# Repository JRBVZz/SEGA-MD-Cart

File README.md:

#### SEGA MD Cart - картридж для SEGA MegaDrive/Genesis

Простой картридж объемом до 4MB (32Mbit) без сохранений, который можно перезаписывать с помощью программатора [FlashKit MD](https://github.com/JRBVZz/Flashkit-MD).

10.02.2026. Добавил проект PCB с возможностью установки памяти MX29L3211 в корпусе SOP-44.

Для хранения данных используется flash память в корпусе TSOP-48 - S29GL032, MX29LV320, M29W320 и др. Для игр до 2MB можно использовать память меньшего объема.

**Параметры для изготовления PCB**  
* 2 слоя
* Толщина PCB: 1.6 мм
* Рекомендуется ENIG покрытие контактов краевого разъема

**Схемы**  
[Schematic PDF](SEGA-Cart-Info/SEGA-Cart-Schematic.pdf)  
[Schematic PDF SOP](SEGA-Cart-Info/SEGA-Cart-SOP-Schematic.pdf)

**Интерактивный BOM**  
[BoM](SEGA-Cart-Info/SEGA-Cart-iBOM.html) (для корректного просмотра нужно скачать raw файл)  
[BoM-SOP](SEGA-Cart-Info/SEGA-Cart-SOP-iBOM.html) (для корректного просмотра нужно скачать raw файл)

Проект создан в [**KiCad 9**](https://www.kicad.org/).

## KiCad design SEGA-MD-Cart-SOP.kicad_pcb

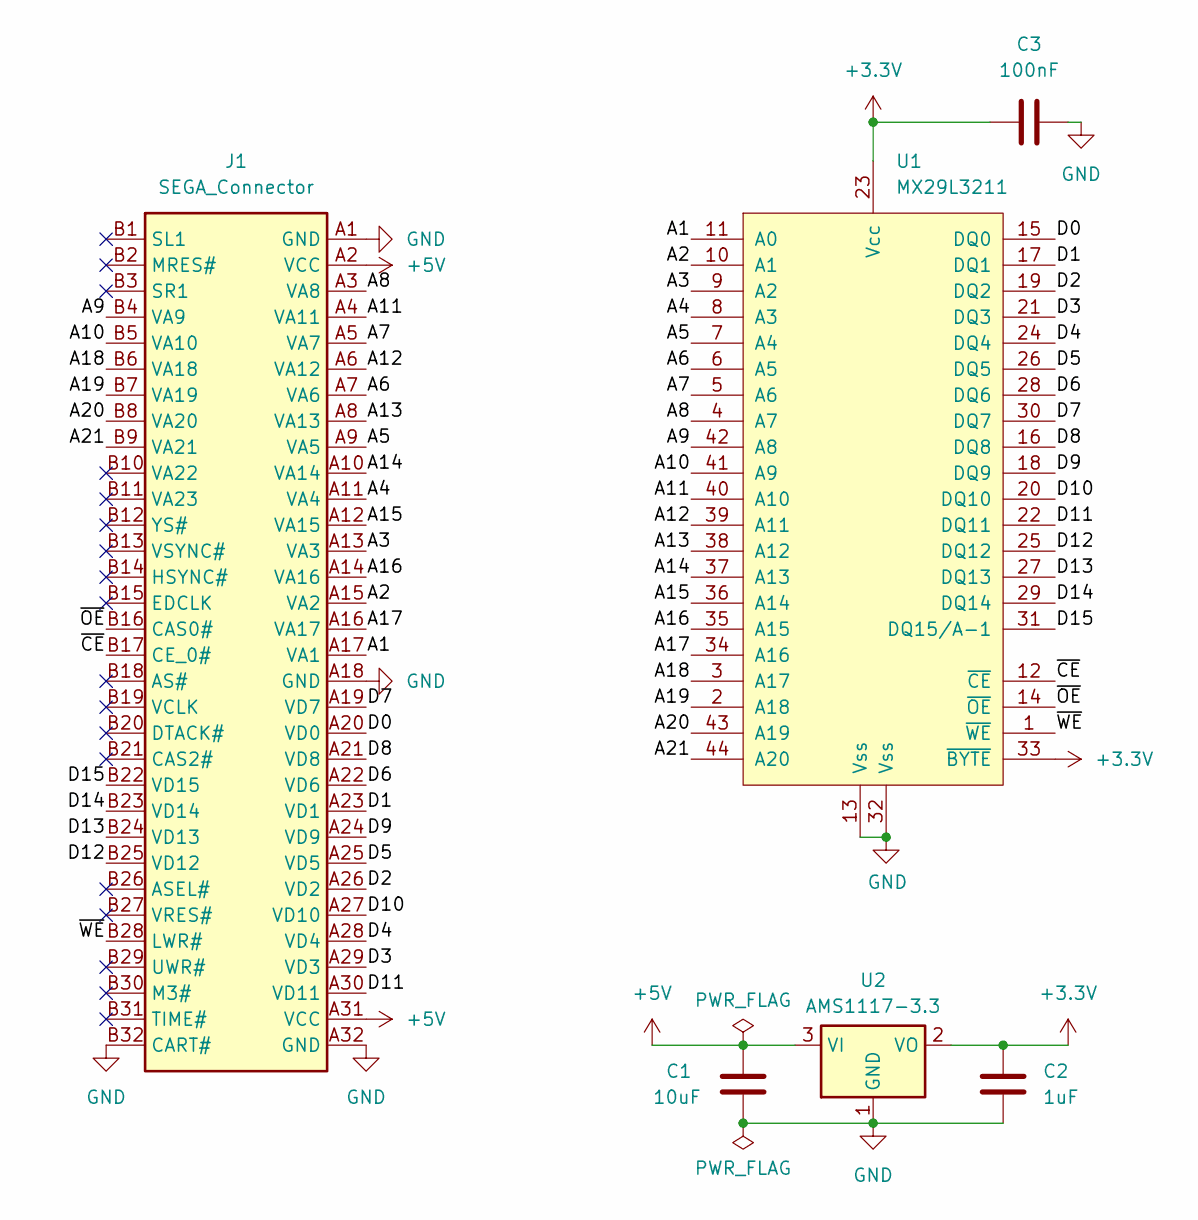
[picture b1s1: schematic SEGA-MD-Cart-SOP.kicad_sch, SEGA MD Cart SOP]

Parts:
C1: 10uF; C_0805_2012Metric_Pad1.18x1.45mm_HandSolder
C2: 1uF; C_0805_2012Metric_Pad1.18x1.45mm_HandSolder
C3: 100nF; C_0805_2012Metric_Pad1.18x1.45mm_HandSolder
J1: SEGA_Connector
U1: MX29L3211; SOP-44_P1.27mm_HandSolder
U2: AMS1117-3.3; SOT-223-3_TabPin2

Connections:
+3.3V: C2.1, C3.2, U1.23 (Vcc), U1.33 (~BYTE), U2.2 (VO)
+5V: C1.1, J1.A2 (VCC), J1.A31 (VCC), U2.3 (VI)
/A1: J1.A17 (VA1), U1.11 (A0)
/A2: J1.A15 (VA2), U1.10 (A1)
/A3: J1.A13 (VA3), U1.9 (A2)
/A4: J1.A11 (VA4), U1.8 (A3)
/A5: J1.A9 (VA5), U1.7 (A4)
/A6: J1.A7 (VA6), U1.6 (A5)
/A7: J1.A5 (VA7), U1.5 (A6)
/A8: J1.A3 (VA8), U1.4 (A7)
/A9: J1.B4 (VA9), U1.42 (A8)
/A10: J1.B5 (VA10), U1.41 (A9)
/A11: J1.A4 (VA11), U1.40 (A10)
/A12: J1.A6 (VA12), U1.39 (A11)
/A13: J1.A8 (VA13), U1.38 (A12)
/A14: J1.A10 (VA14), U1.37 (A13)
/A15: J1.A12 (VA15), U1.36 (A14)
/A16: J1.A14 (VA16), U1.35 (A15)
/A17: J1.A16 (VA17), U1.34 (A16)
/A18: J1.B6 (VA18), U1.3 (A17)
/A19: J1.B7 (VA19), U1.2 (A18)
/A20: J1.B8 (VA20), U1.43 (A19)
/A21: J1.B9 (VA21), U1.44 (A20)
/D0: J1.A20 (VD0), U1.15 (DQ0)
/D1: J1.A23 (VD1), U1.17 (DQ1)
/D2: J1.A26 (VD2), U1.19 (DQ2)
/D3: J1.A29 (VD3), U1.21 (DQ3)
/D4: J1.A28 (VD4), U1.24 (DQ4)
/D5: J1.A25 (VD5), U1.26 (DQ5)
/D6: J1.A22 (VD6), U1.28 (DQ6)
/D7: J1.A19 (VD7), U1.30 (DQ7)
/D8: J1.A21 (VD8), U1.16 (DQ8)
/D9: J1.A24 (VD9), U1.18 (DQ9)
/D10: J1.A27 (VD10), U1.20 (DQ10)
/D11: J1.A30 (VD11), U1.22 (DQ11)
/D12: J1.B25 (VD12), U1.25 (DQ12)
/D13: J1.B24 (VD13), U1.27 (DQ13)
/D14: J1.B23 (VD14), U1.29 (DQ14)
/D15: J1.B22 (VD15), U1.31 (DQ15/A-1)
/~CE: J1.B17 (CE_0#), U1.12 (~CE)
/~OE: J1.B16 (CAS0#), U1.14 (~OE)
/~WE: J1.B28 (LWR#), U1.1 (~WE)
GND: C1.2, C2.2, C3.1, J1.A1 (GND), J1.A18 (GND), J1.A32 (GND), J1.B32 (CART#), U1.13 (Vss), U1.32 (Vss), U2.1 (GND)

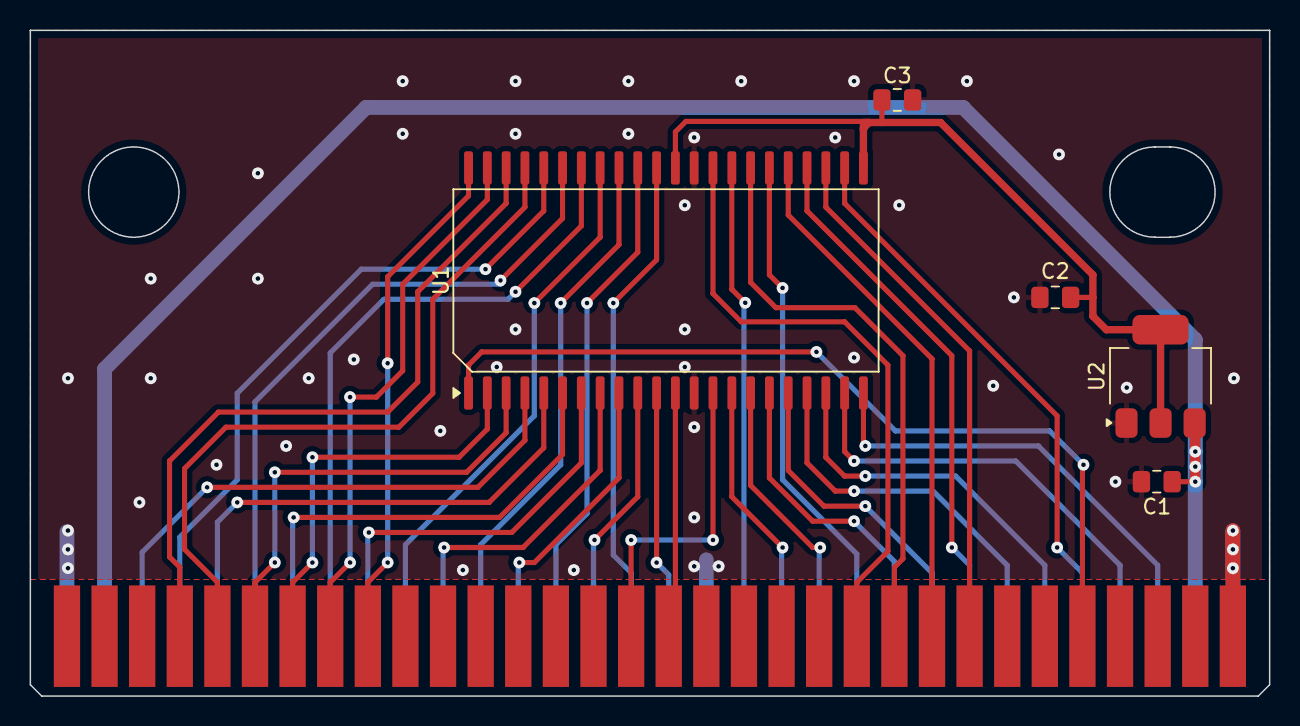
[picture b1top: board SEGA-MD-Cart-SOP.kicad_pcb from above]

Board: 2 copper layers, 83.7 x 45.0 mm, 6 parts (0 on the bottom side), 43 nets.

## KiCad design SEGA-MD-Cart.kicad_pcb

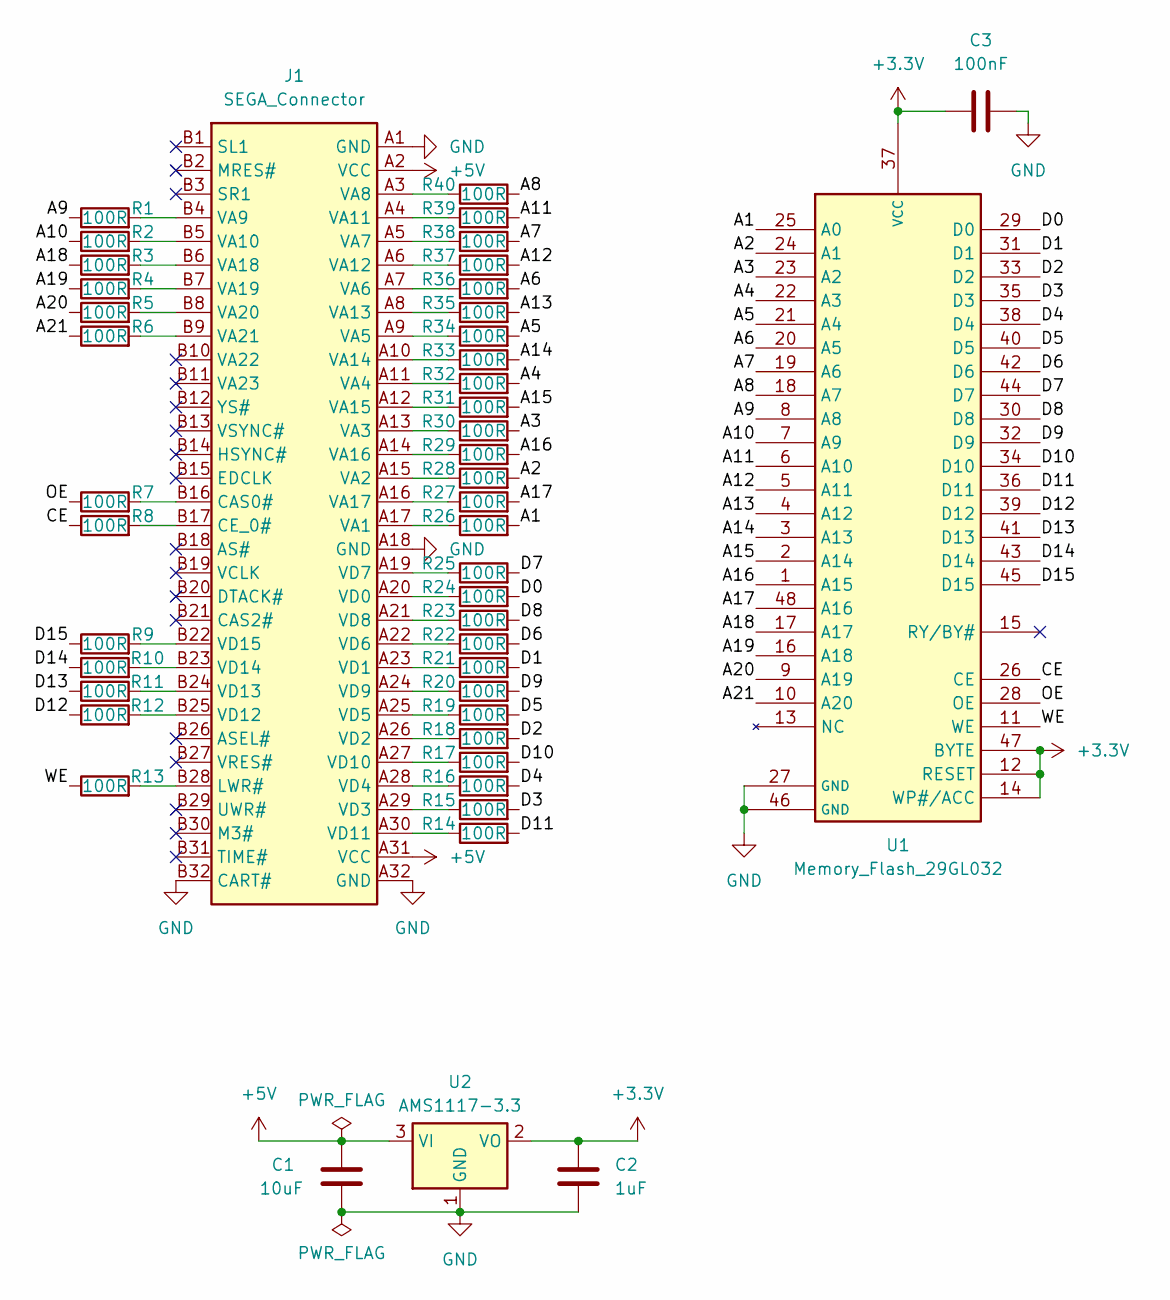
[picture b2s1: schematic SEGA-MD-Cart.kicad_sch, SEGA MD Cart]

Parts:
C1: 10uF; C_0805_2012Metric_Pad1.18x1.45mm_HandSolder
C2: 1uF; C_0805_2012Metric_Pad1.18x1.45mm_HandSolder
C3: 100nF; C_0805_2012Metric_Pad1.18x1.45mm_HandSolder
J1: SEGA_Connector
R1, R2, R3, R4, R5, R6, R7, R8, R9, R10, R11, R12, R13, R14, R15, R16, R17, R18, R19, R20, R21, R22, R23, R24, R25, R26, R27, R28, R29, R30, R31, R32, R33, R34, R35, R36, R37, R38, R39, R40: 100R; R_0805_2012Metric_Pad1.20x1.40mm_HandSolder
U1: Memory_Flash_29GL032; TSOP-I-48_18.4x12mm_P0.5mm
U2: AMS1117-3.3; SOT-223-3_TabPin2

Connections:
+3.3V: C2.1, C3.2, U1.12 (RESET), U1.14 (WP#/ACC), U1.37 (VCC), U1.47 (BYTE), U2.2 (VO)
+5V: C1.1, J1.A2 (VCC), J1.A31 (VCC), U2.3 (VI)
/A1: R26.2, U1.25 (A0)
/A2: R28.2, U1.24 (A1)
/A3: R30.2, U1.23 (A2)
/A4: R32.2, U1.22 (A3)
/A5: R34.2, U1.21 (A4)
/A6: R36.2, U1.20 (A5)
/A7: R38.2, U1.19 (A6)
/A8: R40.2, U1.18 (A7)
/A9: R1.1, U1.8 (A8)
/A10: R2.1, U1.7 (A9)
/A11: R39.2, U1.6 (A10)
/A12: R37.2, U1.5 (A11)
/A13: R35.2, U1.4 (A12)
/A14: R33.2, U1.3 (A13)
/A15: R31.2, U1.2 (A14)
/A16: R29.2, U1.1 (A15)
/A17: R27.2, U1.48 (A16)
/A18: R3.1, U1.17 (A17)
/A19: R4.1, U1.16 (A18)
/A20: R5.1, U1.9 (A19)
/A21: R6.1, U1.10 (A20)
/CE: R8.1, U1.26 (CE)
/D0: R24.2, U1.29 (D0)
/D1: R21.2, U1.31 (D1)
/D2: R18.2, U1.33 (D2)
/D3: R15.2, U1.35 (D3)
/D4: R16.2, U1.38 (D4)
/D5: R19.2, U1.40 (D5)
/D6: R22.2, U1.42 (D6)
/D7: R25.2, U1.44 (D7)
/D8: R23.2, U1.30 (D8)
/D9: R20.2, U1.32 (D9)
/D10: R17.2, U1.34 (D10)
/D11: R14.2, U1.36 (D11)
/D12: R12.1, U1.39 (D12)
/D13: R11.1, U1.41 (D13)
/D14: R10.1, U1.43 (D14)
/D15: R9.1, U1.45 (D15)
/OE: R7.1, U1.28 (OE)
/WE: R13.1, U1.11 (WE)
GND: C1.2, C2.2, C3.1, J1.A1 (GND), J1.A18 (GND), J1.A32 (GND), J1.B32 (CART#), U1.27 (GND), U1.46 (GND), U2.1 (GND)
unnamed: J1.B16 (CAS0#), R7.2
unnamed: J1.B17 (CE_0#), R8.2
unnamed: J1.B28 (LWR#), R13.2
unnamed: J1.A17 (VA1), R26.1
unnamed: J1.A15 (VA2), R28.1
unnamed: J1.A13 (VA3), R30.1
unnamed: J1.A11 (VA4), R32.1
unnamed: J1.A9 (VA5), R34.1
unnamed: J1.A7 (VA6), R36.1
unnamed: J1.A5 (VA7), R38.1
unnamed: J1.A3 (VA8), R40.1
unnamed: J1.B4 (VA9), R1.2
unnamed: J1.B5 (VA10), R2.2
unnamed: J1.A4 (VA11), R39.1
unnamed: J1.A6 (VA12), R37.1
unnamed: J1.A8 (VA13), R35.1
unnamed: J1.A10 (VA14), R33.1
unnamed: J1.A12 (VA15), R31.1
unnamed: J1.A14 (VA16), R29.1
unnamed: J1.A16 (VA17), R27.1
unnamed: J1.B6 (VA18), R3.2
unnamed: J1.B7 (VA19), R4.2
unnamed: J1.B8 (VA20), R5.2
unnamed: J1.B9 (VA21), R6.2
unnamed: J1.A20 (VD0), R24.1
unnamed: J1.A23 (VD1), R21.1
unnamed: J1.A26 (VD2), R18.1
unnamed: J1.A29 (VD3), R15.1
unnamed: J1.A28 (VD4), R16.1
unnamed: J1.A25 (VD5), R19.1
unnamed: J1.A22 (VD6), R22.1
unnamed: J1.A19 (VD7), R25.1
unnamed: J1.A21 (VD8), R23.1
unnamed: J1.A24 (VD9), R20.1
unnamed: J1.A27 (VD10), R17.1
unnamed: J1.A30 (VD11), R14.1
unnamed: J1.B25 (VD12), R12.2
unnamed: J1.B24 (VD13), R11.2
unnamed: J1.B23 (VD14), R10.2
unnamed: J1.B22 (VD15), R9.2

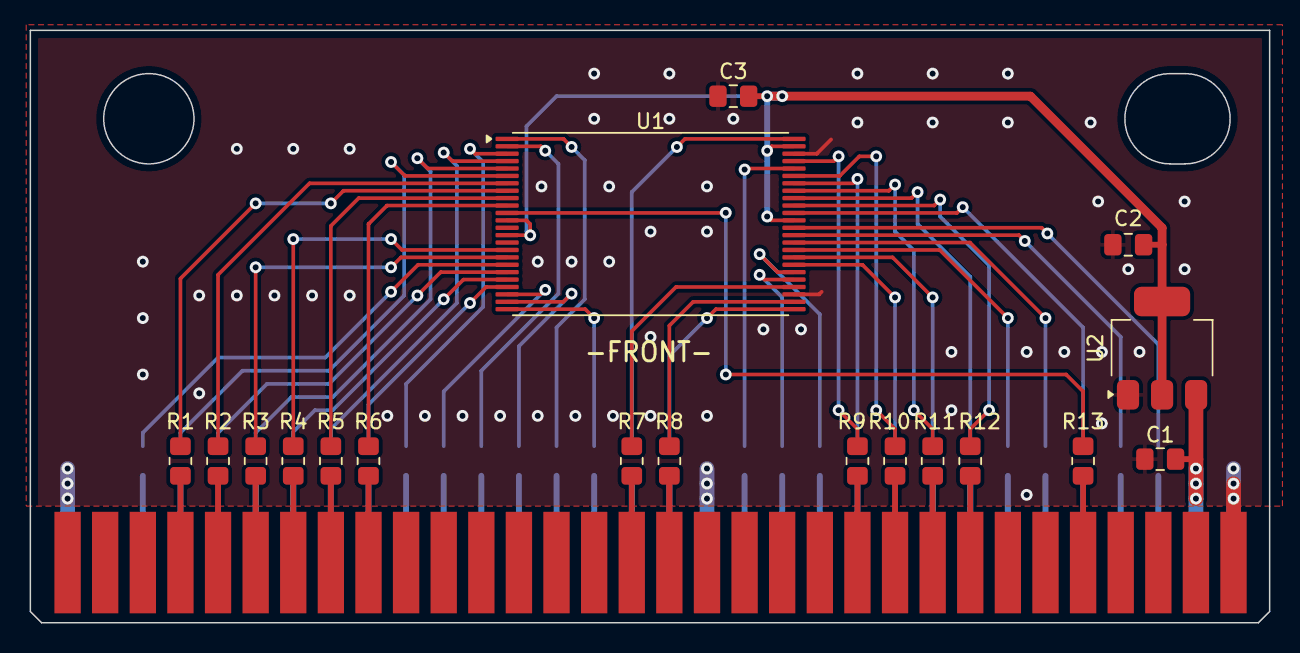
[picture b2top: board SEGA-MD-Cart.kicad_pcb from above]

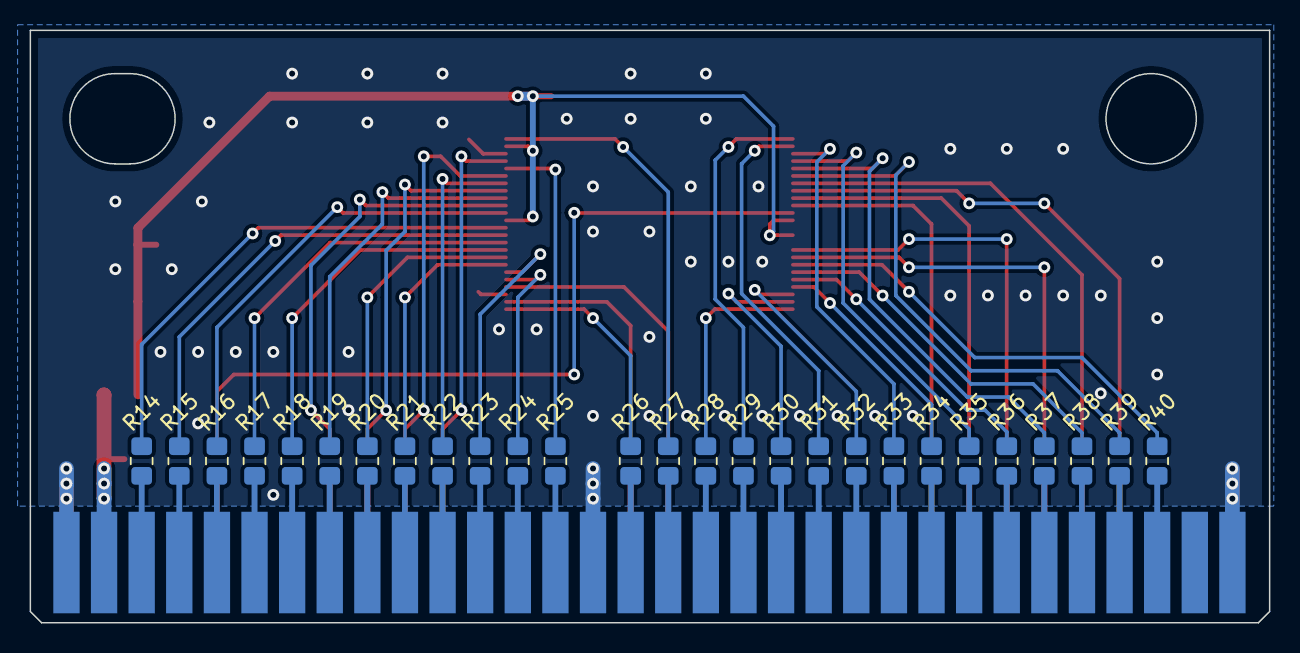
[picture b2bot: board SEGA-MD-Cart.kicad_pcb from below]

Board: 2 copper layers, 83.7 x 40.0 mm, 46 parts (27 on the bottom side), 83 nets.

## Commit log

2026-02-10 Add SOP-44 Project
